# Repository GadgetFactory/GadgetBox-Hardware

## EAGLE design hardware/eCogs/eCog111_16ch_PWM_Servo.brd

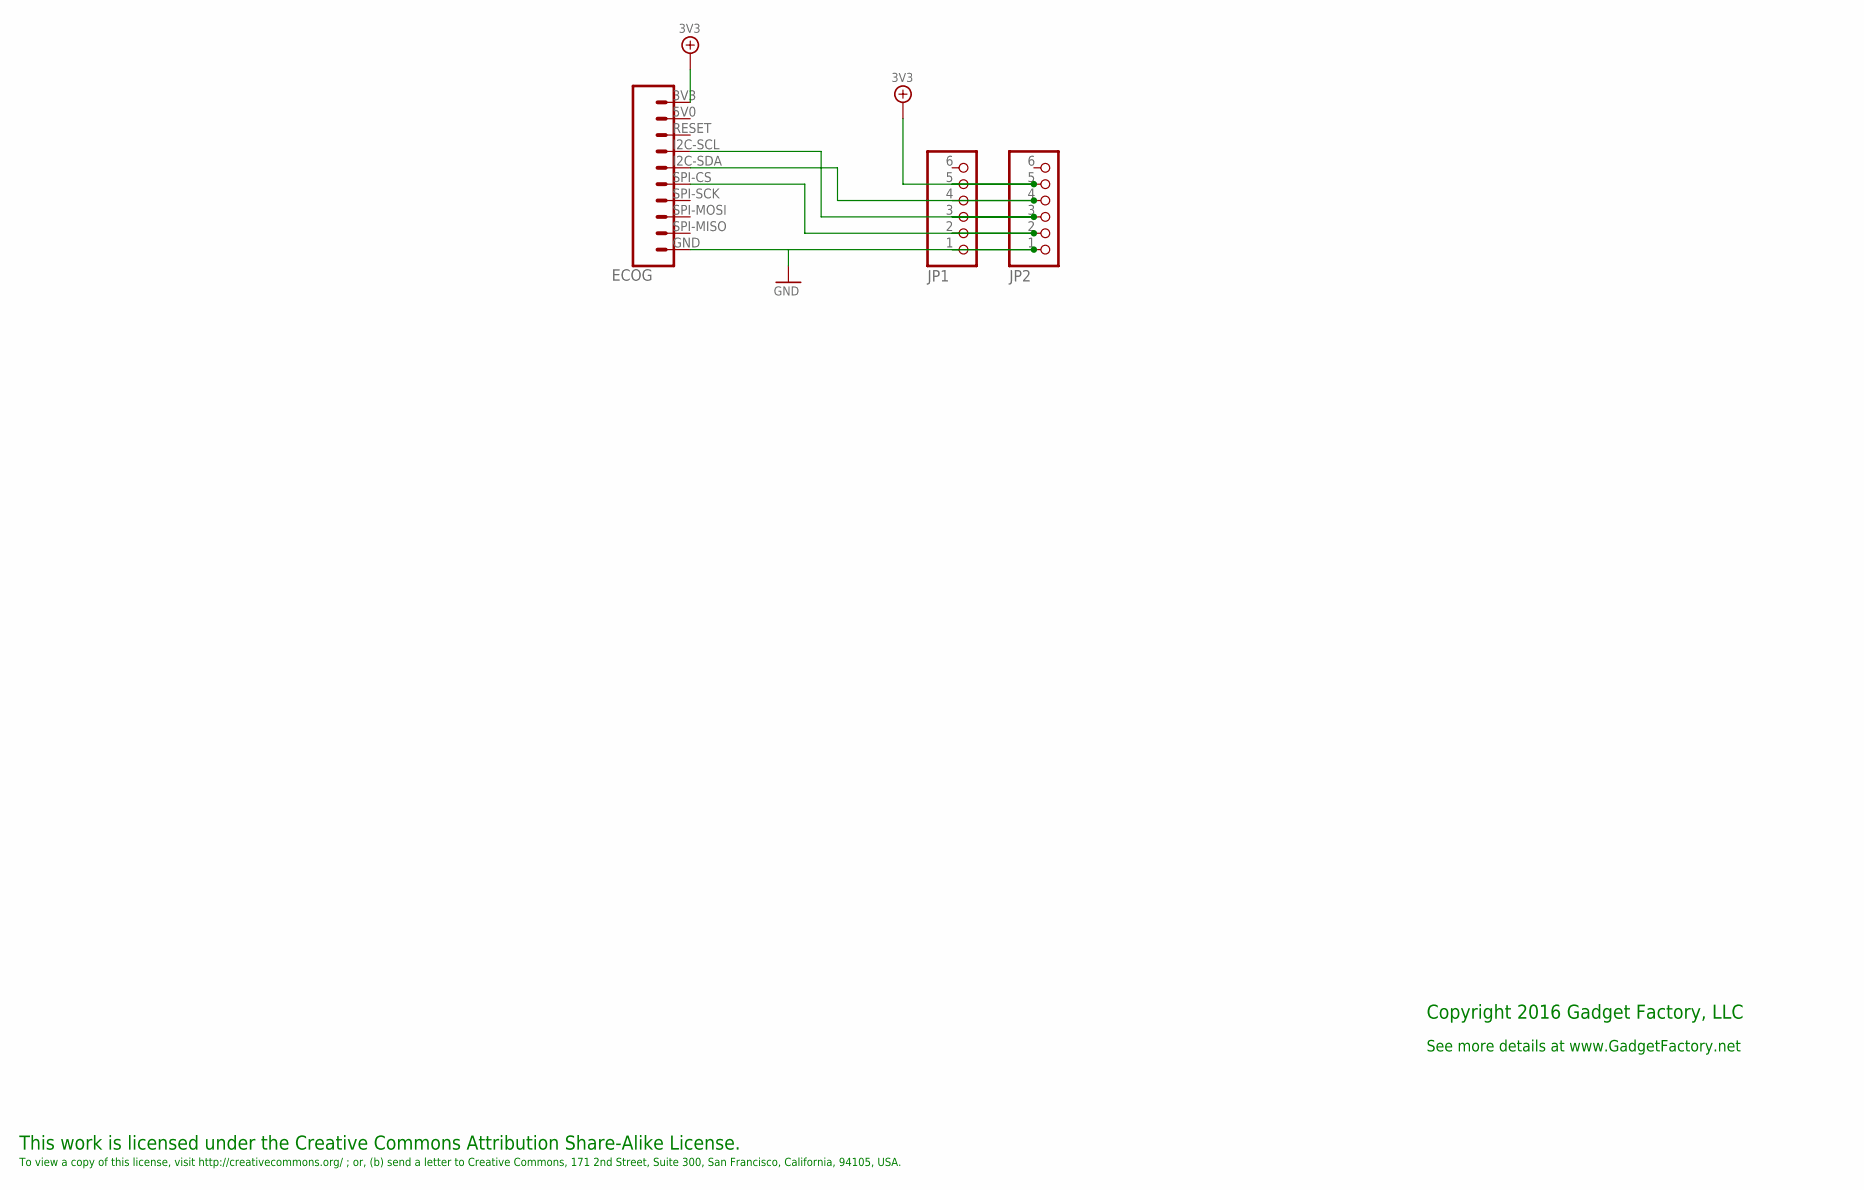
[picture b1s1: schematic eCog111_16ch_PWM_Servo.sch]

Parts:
ECOG: ECOG_BUSES_ROWTHROUGHHOLE; ECOG_BUSES_TH
JP1, JP2: PINHD-1X6; 1X06

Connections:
3V3: ECOG.3V3, JP1.5, JP2.5
GND: ECOG.GND, JP1.1, JP2.1
unnamed: ECOG.SPI-CS, JP1.2, JP2.2
unnamed: ECOG.I2C-SCL, JP1.3, JP2.3
unnamed: ECOG.I2C-SDA, JP1.4, JP2.4

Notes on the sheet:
This work is licensed under the Creative Commons Attribution Share-Alike License.
To view a copy of this license, visit http://creativecommons.org/ ; or, (b) send a letter to Creative Commons, 171 2nd Street, Suite 300, San Francisco, California, 94105, USA.
Copyright 2016 Gadget Factory, LLC
See more details at www.GadgetFactory.net

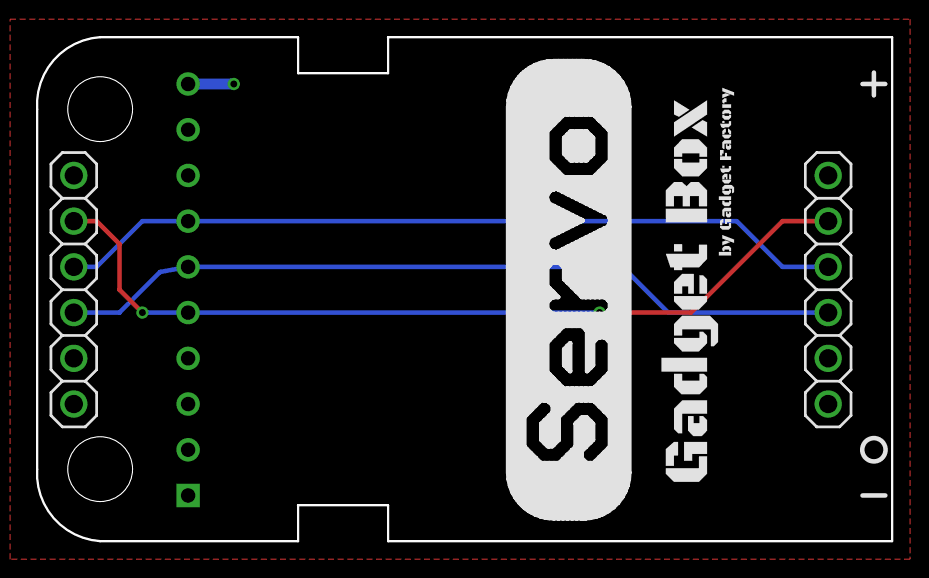
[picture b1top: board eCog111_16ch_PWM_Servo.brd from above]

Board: 2 copper layers, 47.5 x 28.0 mm, 4 parts (0 on the bottom side), 5 nets.

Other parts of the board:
U$2: GADGETBOX_SMALL

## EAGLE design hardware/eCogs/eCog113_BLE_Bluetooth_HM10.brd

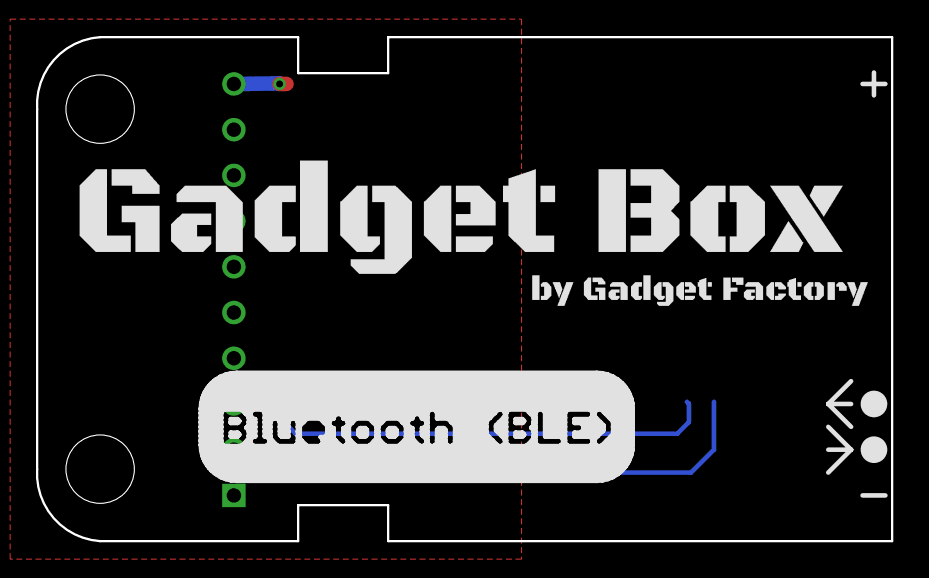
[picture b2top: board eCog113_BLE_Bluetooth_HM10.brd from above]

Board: 2 copper layers, 47.5 x 28.0 mm, 5 parts (1 on the bottom side), 4 nets.

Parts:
E1: HM-10-BOARD; 26.9X13X2.2_BOARD
ECOG: ECOG_GENERAL_ROWTHROUGHOLE; ECOG_GENERAL_TH
U$1: GADGETBOX_TEXT
U$2, U$3: LEGEND_DIO

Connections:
3V3: E1.11, E1.12, ECOG.3V3
GND: E1.13, E1.14, E1.21, E1.22, ECOG.GND
RX/MOSI: E1.2, ECOG.G1
TX/MISO: E1.1, ECOG.G0

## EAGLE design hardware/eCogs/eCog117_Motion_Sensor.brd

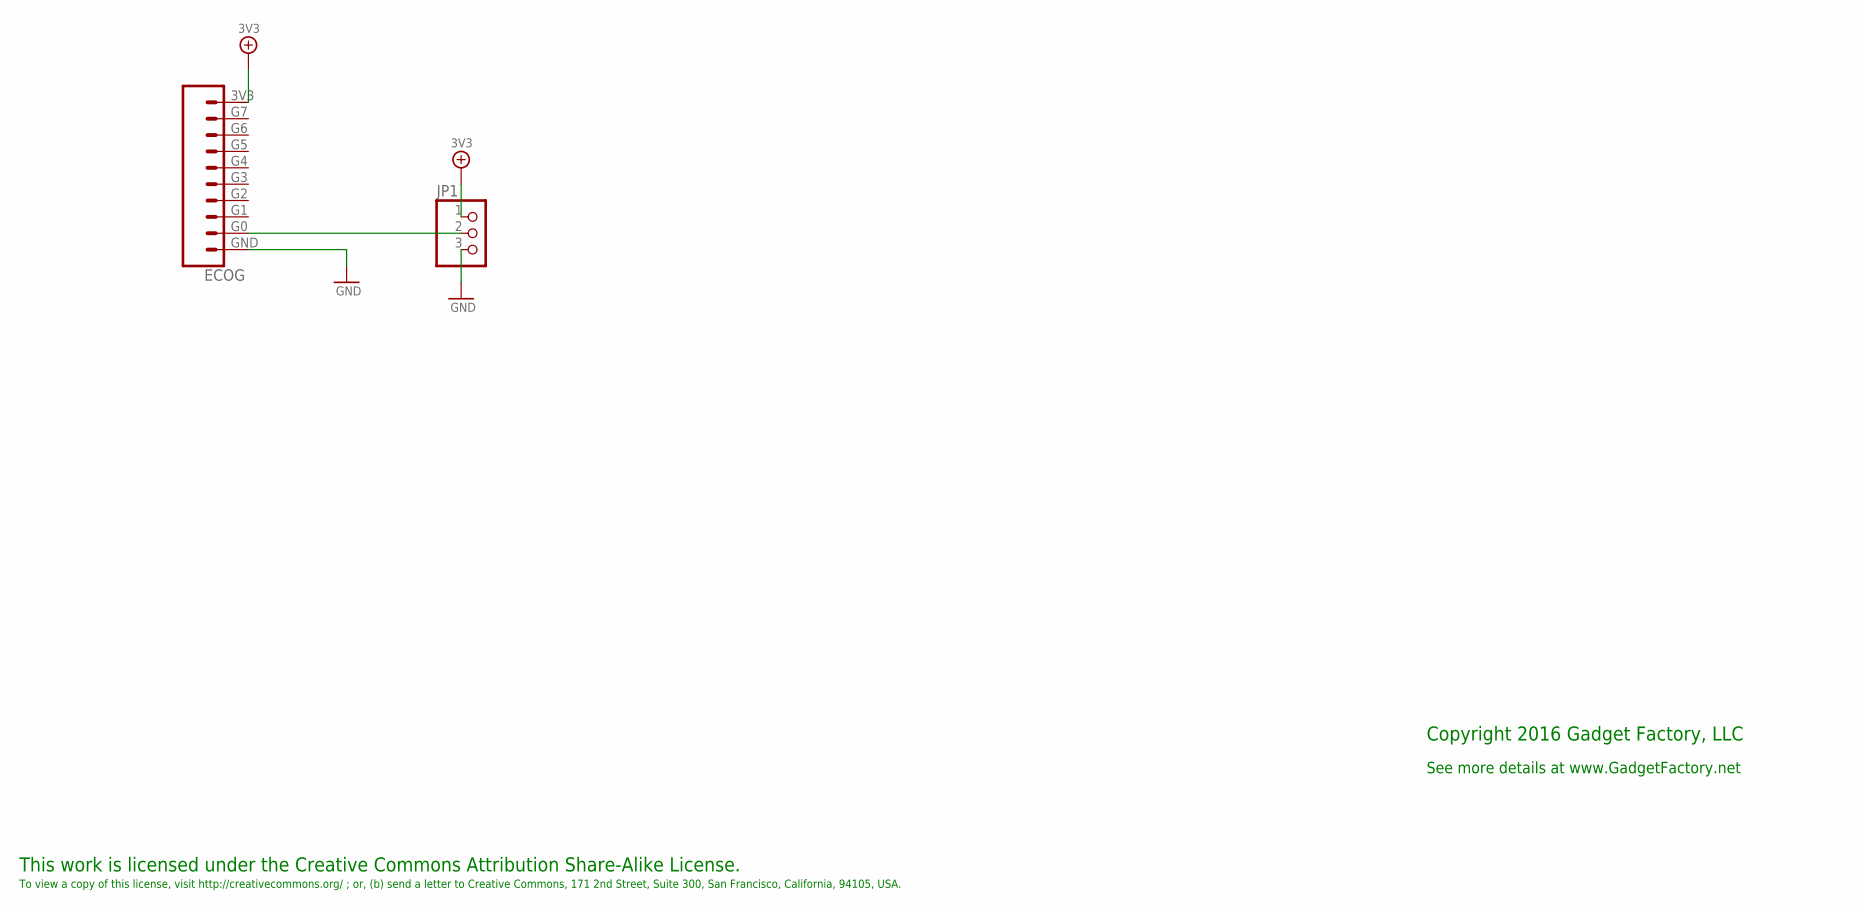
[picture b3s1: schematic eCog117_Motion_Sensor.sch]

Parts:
ECOG: ECOG_GENERAL_ROWTHROUGHOLE; ECOG_GENERAL_TH
JP1: PINHD-1X3; 1X03

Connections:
3V3: ECOG.3V3, JP1.1
GND: ECOG.GND, JP1.3
unnamed: ECOG.G0, JP1.2

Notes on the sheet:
This work is licensed under the Creative Commons Attribution Share-Alike License.
To view a copy of this license, visit http://creativecommons.org/ ; or, (b) send a letter to Creative Commons, 171 2nd Street, Suite 300, San Francisco, California, 94105, USA.
Copyright 2016 Gadget Factory, LLC
See more details at www.GadgetFactory.net

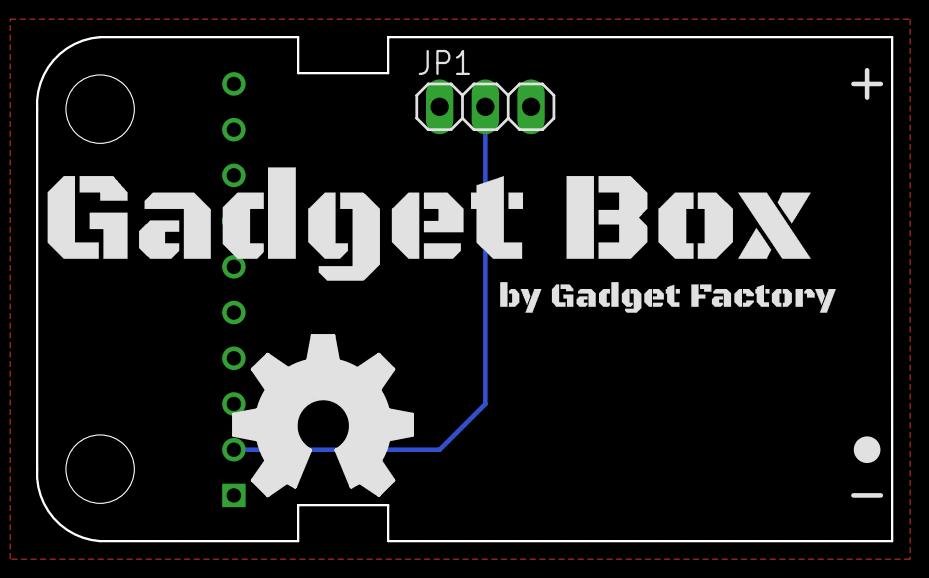
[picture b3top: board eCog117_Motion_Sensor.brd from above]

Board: 2 copper layers, 47.5 x 28.0 mm, 5 parts (0 on the bottom side), 3 nets.

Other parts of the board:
U$1: GADGETBOX_TEXT
U$2: LEGEND_DIO
U$10: OSHW_FILLX350_NOTEXT

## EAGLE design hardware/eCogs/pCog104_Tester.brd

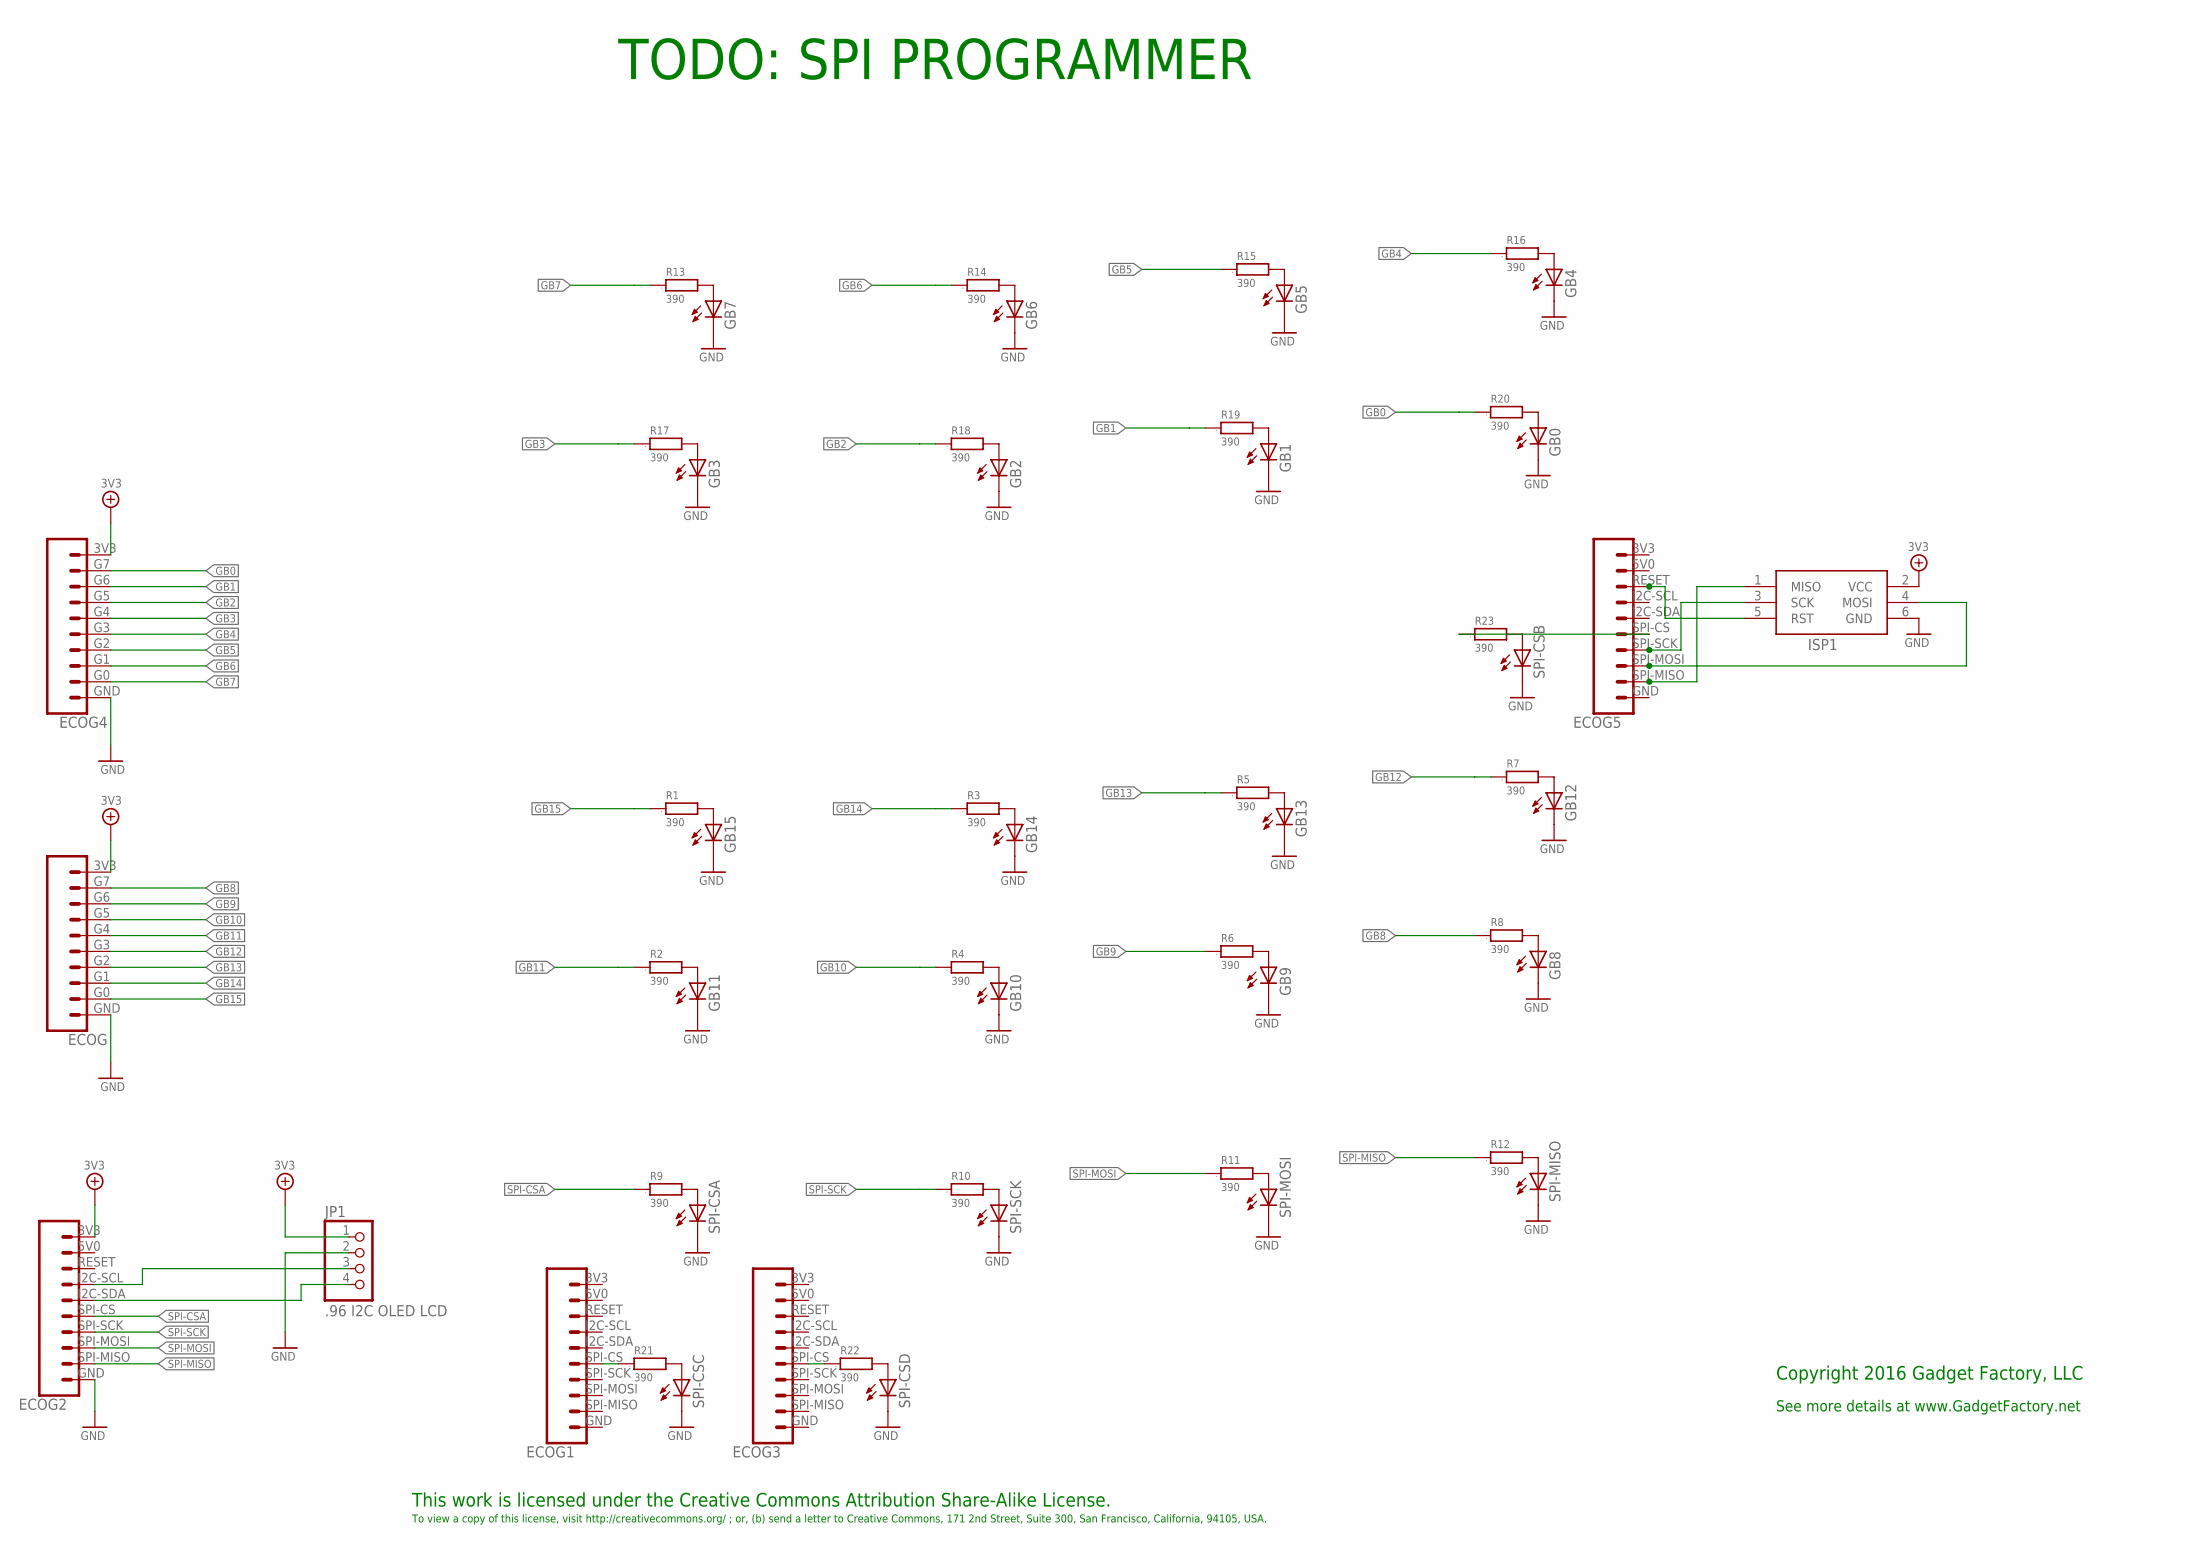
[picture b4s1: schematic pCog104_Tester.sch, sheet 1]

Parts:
ECOG, ECOG4: ECOG_GENERAL_ROWTHROUGHOLE; ECOG_GENERAL_TH; PARTNO NREC010SABC-M30RC,SULLINS CONNECTOR SOL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
ECOG1, ECOG2, ECOG3, ECOG5: ECOG_BUSES_ROWTHROUGHHOLE; ECOG_BUSES_TH; PARTNO NREC010SABC-M30RC,SULLINS CONNECTOR SOL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
GB0, GB1, GB2, GB3, GB4, GB5, GB6, GB7, GB8, GB9, GB10, GB11, GB12, GB13, GB14, GB15: LEDCHIP-LED0805; CHIP-LED0805; PARTNO LTST-C170KGKT,LITE-ON INC (VA),DK,160-1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; DIGIKEY 475-1410-2-ND
ISP1: AVRISP-6; AVRISP
JP1: .96 I2C OLED LCD; 1X04; PARTNO 346540,unknown,dx.com,346540,"0.96"" 12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
R1, R2, R3, R4, R5, R6, R7, R8, R9, R10, R11, R12, R13, R14, R15, R16, R17, R18, R19, R20, R21, R22, R23: 390; 0805; PARTNO MCR10EZPJ391,ROHM SEMICONDUCTOR (PASSIV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; DIGIKEY RMCF0805JT390RCT-ND
SPI-CSA: LEDCHIP-LED0805; CHIP-LED0805; PARTNO LTST-C170KGKT,LITE-ON INC (VA),DK,160-1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; DIGIKEY 475-1410-2-ND
SPI-CSB: LEDCHIP-LED0805; CHIP-LED0805; PARTNO LTST-C170KGKT,LITE-ON INC (VA),DK,160-1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; DIGIKEY 475-1410-2-ND
SPI-CSC: LEDCHIP-LED0805; CHIP-LED0805; PARTNO LTST-C170KGKT,LITE-ON INC (VA),DK,160-1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; DIGIKEY 475-1410-2-ND
SPI-CSD: LEDCHIP-LED0805; CHIP-LED0805; PARTNO LTST-C170KGKT,LITE-ON INC (VA),DK,160-1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; DIGIKEY 475-1410-2-ND
SPI-MISO: LEDCHIP-LED0805; CHIP-LED0805; PARTNO LTST-C170KGKT,LITE-ON INC (VA),DK,160-1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; DIGIKEY 475-1410-2-ND
SPI-MOSI: LEDCHIP-LED0805; CHIP-LED0805; PARTNO LTST-C170KGKT,LITE-ON INC (VA),DK,160-1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; DIGIKEY 475-1410-2-ND
SPI-SCK: LEDCHIP-LED0805; CHIP-LED0805; PARTNO LTST-C170KGKT,LITE-ON INC (VA),DK,160-1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; DIGIKEY 475-1410-2-ND

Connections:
3V3: ECOG.3V3, ECOG2.3V3, ECOG4.3V3, ISP1.2 (VCC), JP1.1
GB0: ECOG4.G7, R20.1
GB1: ECOG4.G6, R19.1
GB2: ECOG4.G5, R18.1
GB3: ECOG4.G4, R17.1
GB4: ECOG4.G3, R16.1
GB5: ECOG4.G2, R15.1
GB6: ECOG4.G1, R14.1
GB7: ECOG4.G0, R13.1
GB8: ECOG.G7, R8.1
GB9: ECOG.G6, R6.1
GB10: ECOG.G5, R4.1
GB11: ECOG.G4, R2.1
GB12: ECOG.G3, R7.1
GB13: ECOG.G2, R5.1
GB14: ECOG.G1, R3.1
GB15: ECOG.G0, R1.1
GND: ECOG.GND, ECOG2.GND, ECOG4.GND, GB0.C, GB1.C, GB2.C, GB3.C, GB4.C, GB5.C, GB6.C, GB7.C, GB8.C, GB9.C, GB10.C, GB11.C, GB12.C, GB13.C, GB14.C, GB15.C, ISP1.6 (GND), JP1.2, SPI-CSA.C, SPI-CSB.C, SPI-CSC.C, SPI-CSD.C, SPI-MISO.C, SPI-MOSI.C, SPI-SCK.C
unnamed: GB15.A, R1.2
unnamed: GB14.A, R3.2
unnamed: GB13.A, R5.2
unnamed: GB12.A, R7.2
unnamed: R9.2, SPI-CSA.A
unnamed: R10.2, SPI-SCK.A
unnamed: ECOG2.I2C-SDA, JP1.4
unnamed: ECOG2.I2C-SCL, JP1.3
unnamed: R11.2, SPI-MOSI.A
unnamed: R12.2, SPI-MISO.A
unnamed: R21.2, SPI-CSC.A
unnamed: GB11.A, R2.2
unnamed: GB10.A, R4.2
unnamed: GB9.A, R6.2
unnamed: GB8.A, R8.2
unnamed: GB7.A, R13.2
unnamed: GB6.A, R14.2
unnamed: GB5.A, R15.2
unnamed: GB4.A, R16.2
unnamed: GB3.A, R17.2
unnamed: GB2.A, R18.2
unnamed: GB1.A, R19.2
unnamed: GB0.A, R20.2
unnamed: R22.2, SPI-CSD.A
unnamed: R23.2, SPI-CSB.A
unnamed: ECOG1.SPI-CS, R21.1
unnamed: ECOG3.SPI-CS, R22.1
unnamed: ECOG5.SPI-CS, R23.1
unnamed: ECOG5.SPI-MISO, ISP1.1 (MISO)
unnamed: ECOG5.SPI-SCK, ISP1.3 (SCK)
unnamed: ECOG5.RESET (RSV), ISP1.5 (RST)
unnamed: ECOG5.SPI-MOSI, ISP1.4 (MOSI)
SPI-CSA: ECOG2.SPI-CS, R9.1
SPI-MISO: ECOG2.SPI-MISO, R12.1
SPI-MOSI: ECOG2.SPI-MOSI, R11.1
SPI-SCK: ECOG2.SPI-SCK, R10.1

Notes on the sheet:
This work is licensed under the Creative Commons Attribution Share-Alike License.
To view a copy of this license, visit http://creativecommons.org/ ; or, (b) send a letter to Creative Commons, 171 2nd Street, Suite 300, San Francisco, California, 94105, USA.
Copyright 2016 Gadget Factory, LLC
See more details at www.GadgetFactory.net
TODO: SPI PROGRAMMER

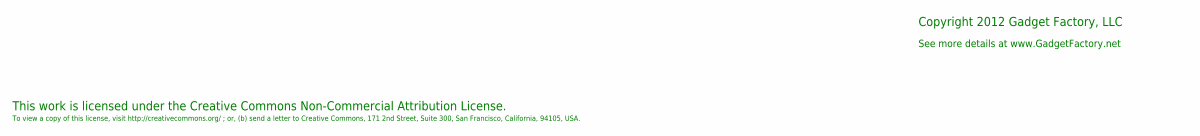
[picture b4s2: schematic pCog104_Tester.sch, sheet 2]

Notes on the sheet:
This work is licensed under the Creative Commons Non-Commercial Attribution License.
To view a copy of this license, visit http://creativecommons.org/ ; or, (b) send a letter to Creative Commons, 171 2nd Street, Suite 300, San Francisco, California, 94105, USA.
Copyright 2012 Gadget Factory, LLC
See more details at www.GadgetFactory.net

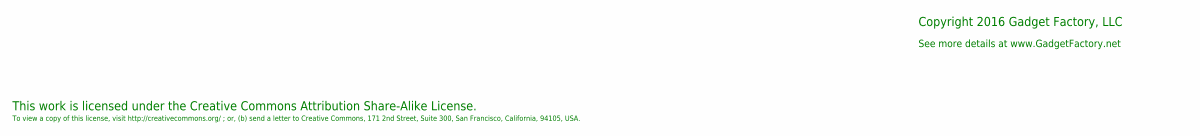
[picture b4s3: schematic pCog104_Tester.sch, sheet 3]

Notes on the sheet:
This work is licensed under the Creative Commons Attribution Share-Alike License.
To view a copy of this license, visit http://creativecommons.org/ ; or, (b) send a letter to Creative Commons, 171 2nd Street, Suite 300, San Francisco, California, 94105, USA.
Copyright 2016 Gadget Factory, LLC
See more details at www.GadgetFactory.net

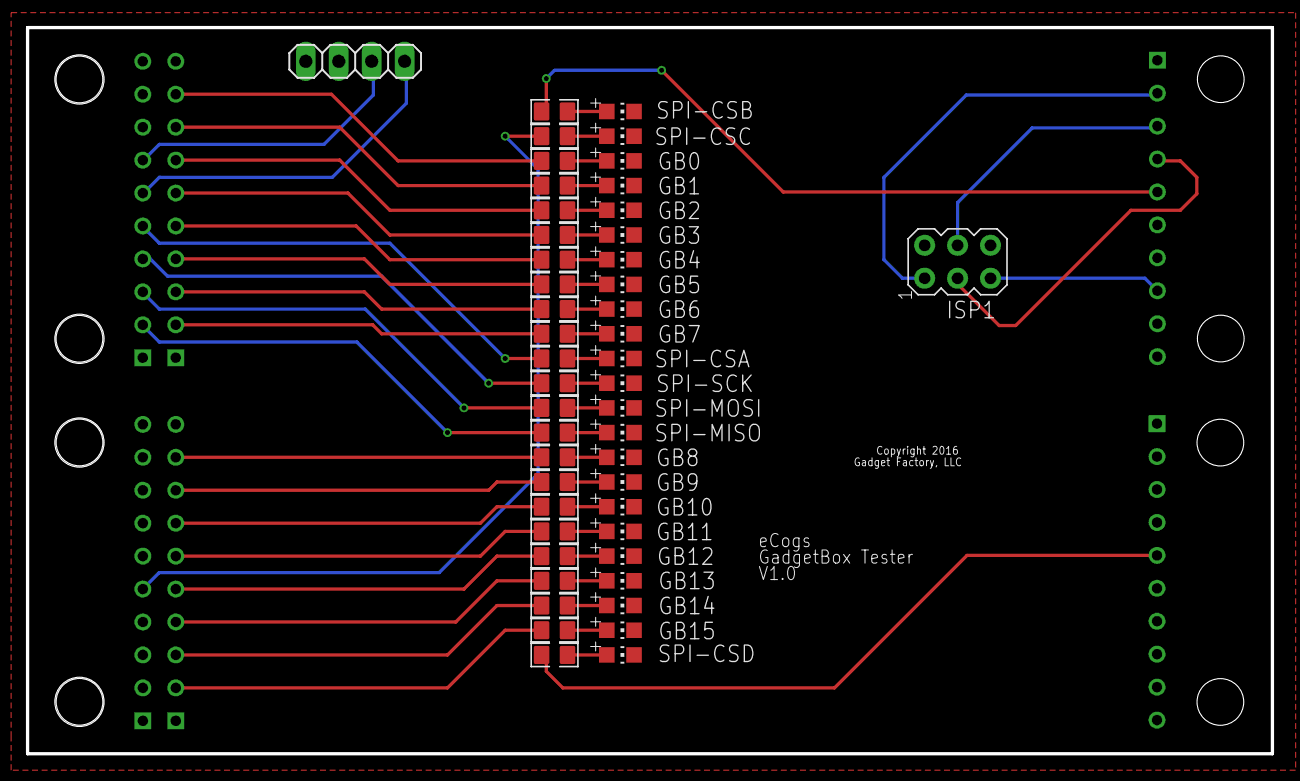
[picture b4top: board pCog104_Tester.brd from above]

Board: 2 copper layers, 96.0 x 56.0 mm, 54 parts (0 on the bottom side), 54 nets.
